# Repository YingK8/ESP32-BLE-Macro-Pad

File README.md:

# ESP32 BLE HID Macropad

A compact, programmable macropad with Bluetooth connectivity, featuring 6 mechanical keys and a rotary encoder for media control.

## Features

- 6-key mechanical switch matrix
- Rotary encoder for volume/scroll control
- Bluetooth HID (no drivers required)
- ST7789 240×280 screen driven by a desktop companion app over USB
- Productivity apps — pomodoro, class/assignment agenda, now playing, system stats —
  that live on the PC, so adding one needs no reflashing

## Hardware

| Component | Quantity |
|-----------|----------|
| ESP32-C3 Dev Board | 1 |
| Mechanical Keyswitches | 6 |
| Rotary Encoder | 1 |
| 1N4148 Diodes | 6 |
| ST7789 240×280 SPI display | 1 |

## Pinout

Authoritative source is [`macro-pad/include/Config.h`](macro-pad/include/Config.h).

| Function | ESP32 Pin |
|----------|-----------|
| Row 1 | GPIO 1 |
| Row 2 | GPIO 5 |
| Col 1 | GPIO 4 |
| Col 2 | GPIO 21 |
| Col 3 | GPIO 8 |
| Encoder A | GPIO 3 |
| Encoder B | GPIO 10 |
| TFT SCK / MOSI | GPIO 7 / 6 |
| TFT DC / CS / RST | GPIO 2 / 0 / 9 |
| TFT backlight | GPIO 20 |

> GPIO21 is UART0 TX on the ESP32-C3. The `ARDUINO_USB_CDC_ON_BOOT` build flag
> routes `Serial` to native USB to free it; if the two column-1 keys do not
> register, that pin is the reason.

## Installation

1. Wire components according to the pinout table.
2. Flash the firmware (PlatformIO pulls the libraries itself):
   ```bash
   cd macro-pad && pio run -t upload
   ```
3. Set up the desktop app:
   ```bash
   cd macro-pad/host && uv sync && uv run macropad run
   ```

## Usage

1. Power on the macropad and pair with "ESP32 MacroPad" via Bluetooth — this
   carries the keyboard macros.
2. Plug it in over USB — this carries the screen. The menubar icon shows the link
   state and lets you switch apps.
3. Default layout:

   | | Col 1 (GPIO4) | Col 2 (GPIO21) | Col 3 (GPIO8) |
   |---|---|---|---|
   | **Row 1** | previous app | ⌘⇧4 screenshot | next app |
   | **Row 2** | action A | ⌘Space Spotlight | action B |

   The encoder controls volume, unless the active app asks for it.

## Architecture

The pad is a dumb character-cell terminal: the PC renders each app to text lines
and pushes finished frames down the wire, and the pad reports key and encoder
events back. App logic, API tokens and text never touch the ESP32, which is what
keeps the firmware at ~48% of the C3's 1.25 MB app slot no matter how many apps
exist.

- [`macro-pad/PROTOCOL.md`](macro-pad/PROTOCOL.md) — wire format, key ids, grid maths
- [`macro-pad/host/README.md`](macro-pad/host/README.md) — desktop app, apps, writing your own

## Customization

Macro keys are the `Key::combo(...)` entries in
[`macro-pad/src/main.cpp`](macro-pad/src/main.cpp); `Key::app(...)` entries are
forwarded to the host instead of being typed. Everything else — what each screen
shows, what the action keys do — is Python in `macro-pad/host/`.

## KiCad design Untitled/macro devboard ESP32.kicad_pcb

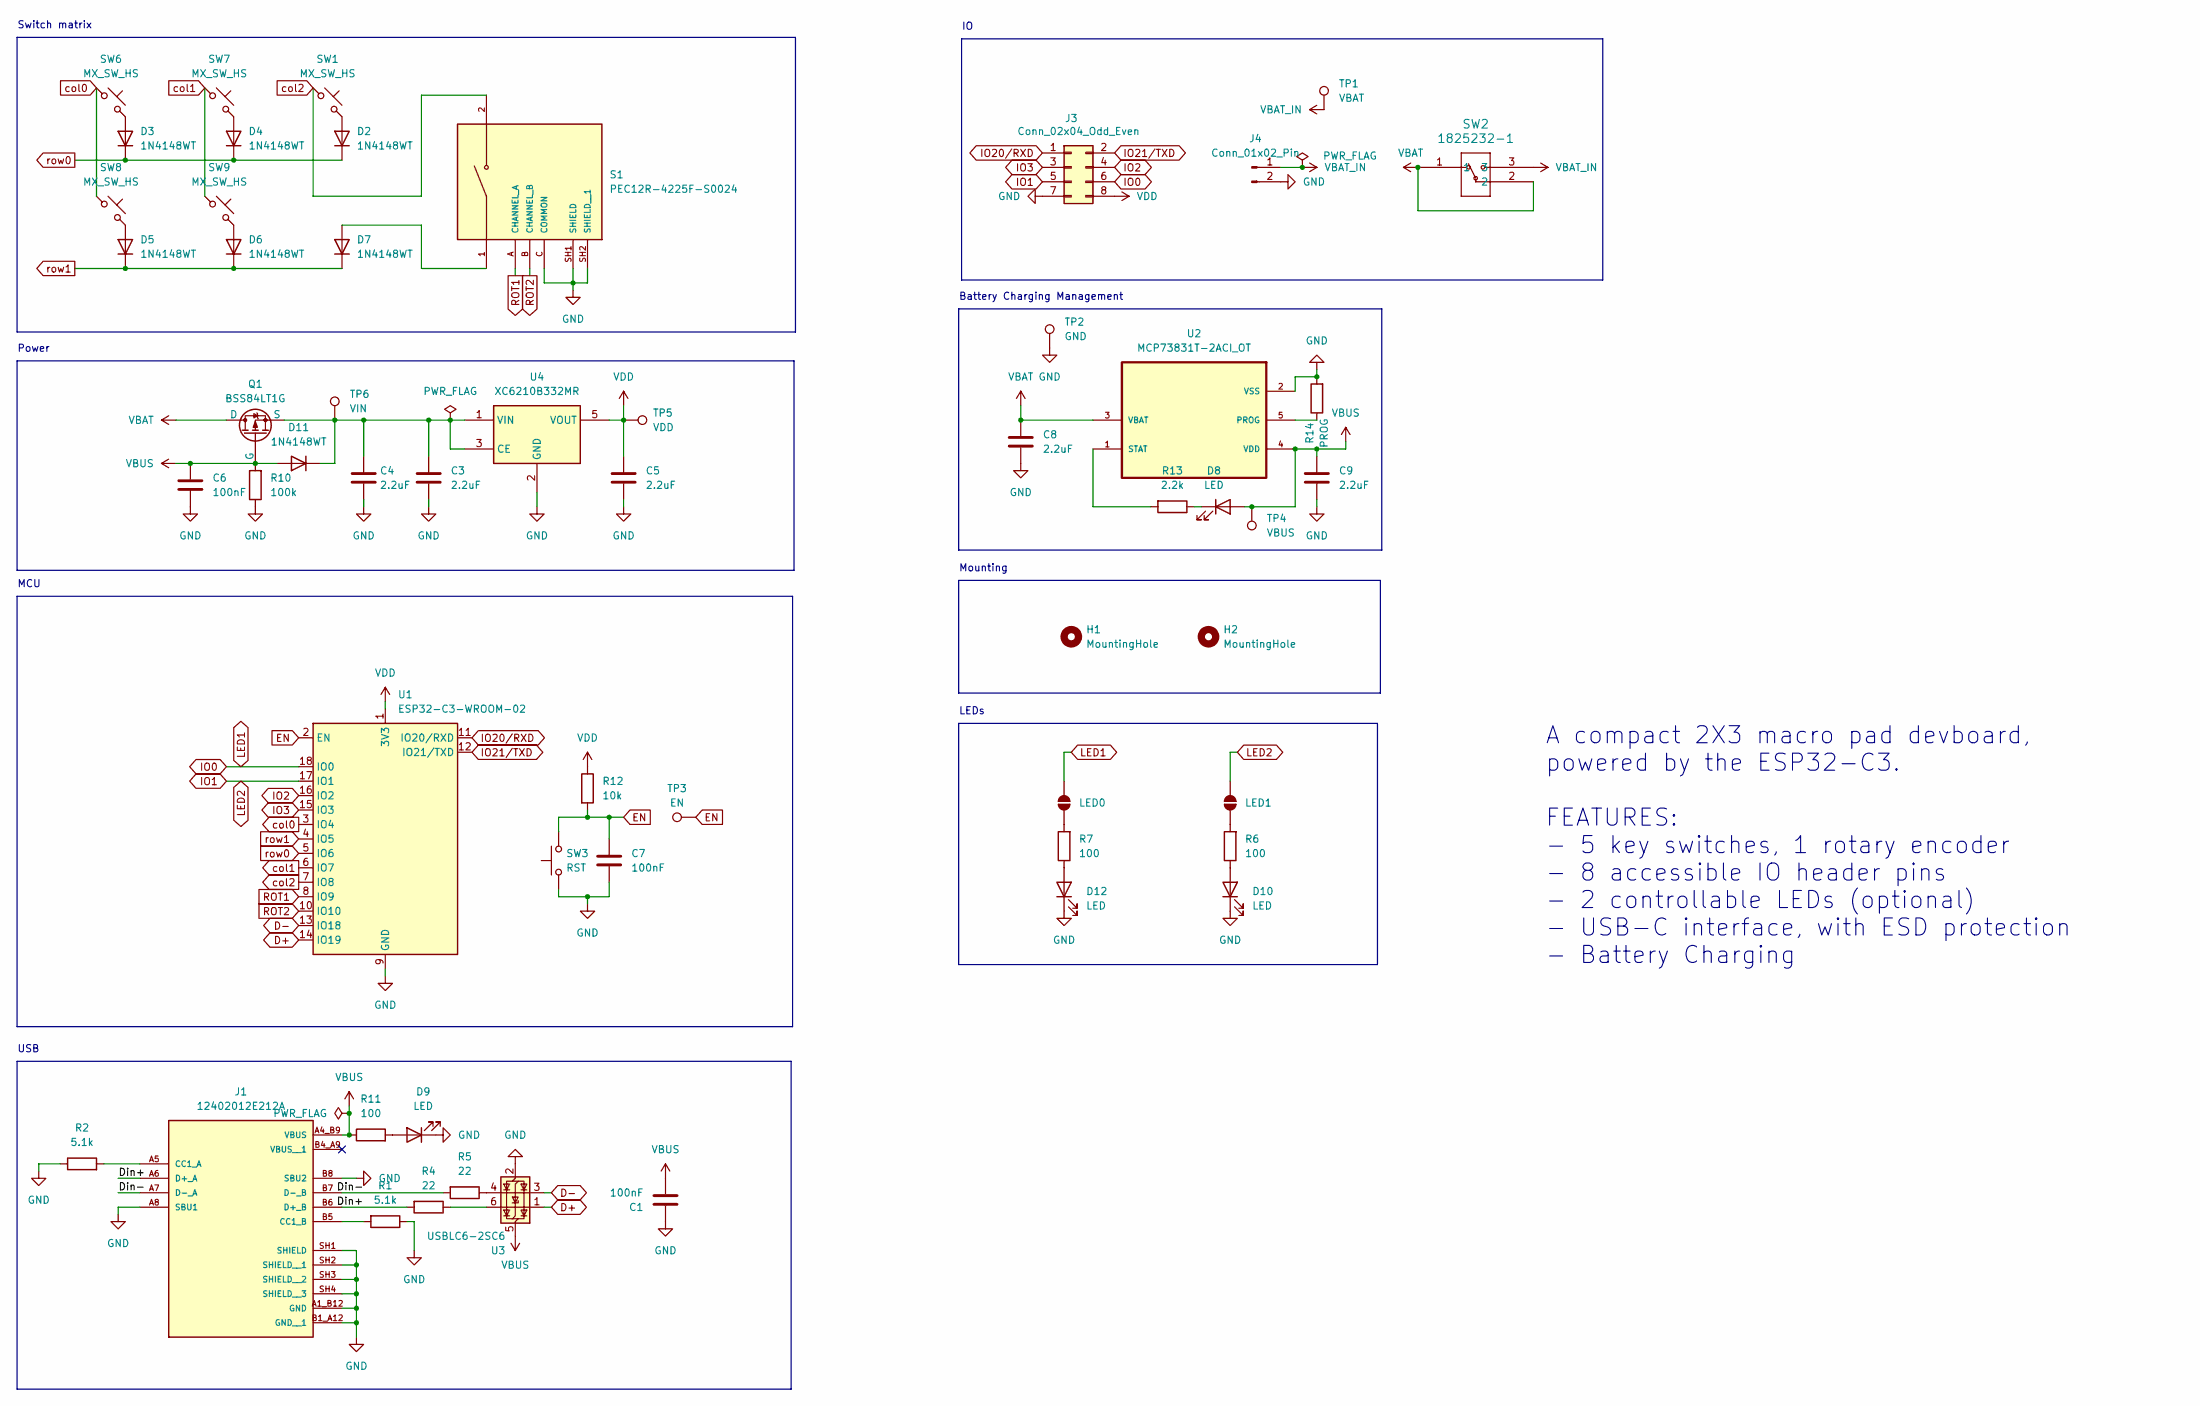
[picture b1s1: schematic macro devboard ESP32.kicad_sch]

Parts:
C1, C6, C7: 100nF; C_0603_1608Metric_Pad1.08x0.95mm_HandSolder
C3, C4, C5, C8, C9: 2.2uF; C_0603_1608Metric_Pad1.08x0.95mm_HandSolder
D2, D3, D4, D5, D6, D7, D11: 1N4148WT; D_SOD-323F
D8, D9, D10, D12: LED; LED_0805_2012Metric_Pad1.15x1.40mm_HandSolder
H1, H2: MountingHole; MountingHole_2.7mm_M2.5
J1: 12402012E212A; AMPHENOL_12402012E212A; PARTREV 4
J3: Conn_02x04_Odd_Even; PinSocket_2x04_P2.54mm_Vertical
J4: Conn_01x02_Pin; JST_PH_S2B-PH-K_1x02_P2.00mm_Horizontal
LED0, LED1: SolderJumper_2_Open; SolderJumper-2_P1.3mm_Open_RoundedPad1.0x1.5mm
Q1: BSS84LT1G; TSOT-23_HandSoldering
R1, R2: 5.1k; R_0603_1608Metric_Pad0.98x0.95mm_HandSolder
R4, R5: 22; R_0603_1608Metric_Pad0.98x0.95mm_HandSolder
R6, R7, R11: 100; R_0603_1608Metric_Pad0.98x0.95mm_HandSolder
R10: 100k; R_0603_1608Metric_Pad0.98x0.95mm_HandSolder
R12: 10k; R_0603_1608Metric_Pad0.98x0.95mm_HandSolder
R13: 2.2k; R_0603_1608Metric_Pad0.98x0.95mm_HandSolder
R14: PROG; R_0603_1608Metric_Pad0.98x0.95mm_HandSolder
S1: PEC12R-4225F-S0024; XDCR_PEC12R-4225F-S0024; PARTREV 07/21
SW1, SW6, SW7, SW8, SW9: MX_SW_HS; Kailh_socket_MX_optional
SW2: 1825232-1; 1825232-1_TEC
SW3: RST; SW_Tactile_SPST_NO_Straight_CK_PTS636Sx25SMTRLFS
TP1: VBAT; TestPoint_Pad_D2.0mm
TP2: GND; TestPoint_Pad_D2.0mm
TP3: EN; TestPoint_Pad_D2.0mm
TP4: VBUS; TestPoint_Pad_D2.0mm
TP5: VDD; TestPoint_Pad_D2.0mm
TP6: VIN; TestPoint_Pad_D2.0mm
U1: ESP32-C3-WROOM-02
U2: MCP73831T-2ACI_OT; SOT95P280X145-5N; MPN MCP73831T-2ACI/OT
U3: USBLC6-2SC6; SOT-23-6_Handsoldering
U4: XC6210B332MR; SC-74A-5_1.55x2.9mm_P0.95mm

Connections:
/Din+: J1.A6 (D+_A), J1.B6 (D+_B), R4.2
/Din-: J1.A7 (D-_A), J1.B7 (D-_B), R5.2
D+: U1.14 (IO19), U3.1 (I/O1)
D-: U1.13 (IO18), U3.3 (I/O2)
EN: C7.2, R12.2, SW3.2, TP3.1, U1.2 (EN)
GND: C1.2, C3.1, C4.1, C5.1, C6.1, C7.1, C8.1, C9.2, D9.1 (K), D10.1 (K), D12.1 (K), J1.A1_B12 (GND), J1.A8 (SBU1), J1.B1_A12 (GND__1), J1.B8 (SBU2), J1.SH1 (SHIELD), J1.SH2 (SHIELD__1), J1.SH3 (SHIELD__2), J1.SH4 (SHIELD__3), J3.7, J4.2, R1.1, R2.1, R10.1, R14.2, S1.C (COMMON), S1.SH1 (SHIELD), S1.SH2 (SHIELD__1), SW3.1, TP2.1, U1.9 (GND), U1.19 (GND), U2.2 (VSS), U3.2 (GND), U4.2 (GND)
IO0: J3.6, LED0.2 (B), U1.18 (IO0)
IO1: J3.5, LED1.2 (B), U1.17 (IO1)
IO2: J3.4, U1.16 (IO2)
IO3: J3.3, U1.15 (IO3)
IO20/RXD: J3.1, U1.11 (IO20/RXD)
IO21/TXD: J3.2, U1.12 (IO21/TXD)
unnamed: D2.2 (A), SW1.2
unnamed: D3.2 (A), SW6.2
unnamed: D4.2 (A), SW7.2
unnamed: D5.2 (A), SW8.2
unnamed: D6.2 (A), SW9.2
unnamed: D7.2 (A), S1.1
unnamed: D8.1 (K), R13.1
unnamed: D9.2 (A), R11.2
unnamed: D10.2 (A), R6.1
unnamed: C3.2, C4.2, D11.1 (K), Q1.2 (S), TP6.1, U4.1 (VIN), U4.3 (CE)
unnamed: D12.2 (A), R7.1
unnamed: J1.A5 (CC1_A), R2.2
unnamed: J1.B5 (CC1_B), R1.2
unnamed: LED0.1 (A), R7.2
unnamed: LED1.1 (A), R6.2
unnamed: R4.1, U3.6 (I/O1)
unnamed: R5.1, U3.4 (I/O2)
unnamed: R14.1, U2.5 (PROG)
unnamed: R13.2, U2.1 (STAT)
ROT1: S1.A (CHANNEL_A), U1.8 (IO9)
ROT2: S1.B (CHANNEL_B), U1.10 (IO10)
VBAT: C8.2, Q1.3 (D), SW2.1, SW2.2, U2.3 (VBAT)
VBAT_IN: J4.1, SW2.3, TP1.1
VBUS: C1.1, C6.2, C9.1, D8.2 (A), D11.2 (A), J1.A4_B9 (VBUS), Q1.1 (G), R10.2, R11.1, TP4.1, U2.4 (VDD), U3.5 (VBUS)
VDD: C5.2, J3.8, R12.1, TP5.1, U1.1 (3V3), U4.5 (VOUT)
col0: SW6.1, SW8.1, U1.3 (IO4)
col1: SW7.1, SW9.1, U1.6 (IO7)
col2: S1.2, SW1.1, U1.7 (IO8)
row0: D2.1 (K), D3.1 (K), D4.1 (K), U1.5 (IO6)
row1: D5.1 (K), D6.1 (K), D7.1 (K), U1.4 (IO5)

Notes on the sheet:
LEDs
Mounting
A compact 2X3 macro pad devboard, powered by the ESP32-C3. FEATURES: - 5 key switches, 1 rotary encoder - 8 accessible IO header pins - 2 controllable LEDs (optional) - USB-C interface, with ESD protection - Battery Charging
USB
Power
Switch matrix
MCU
Battery Charging Management

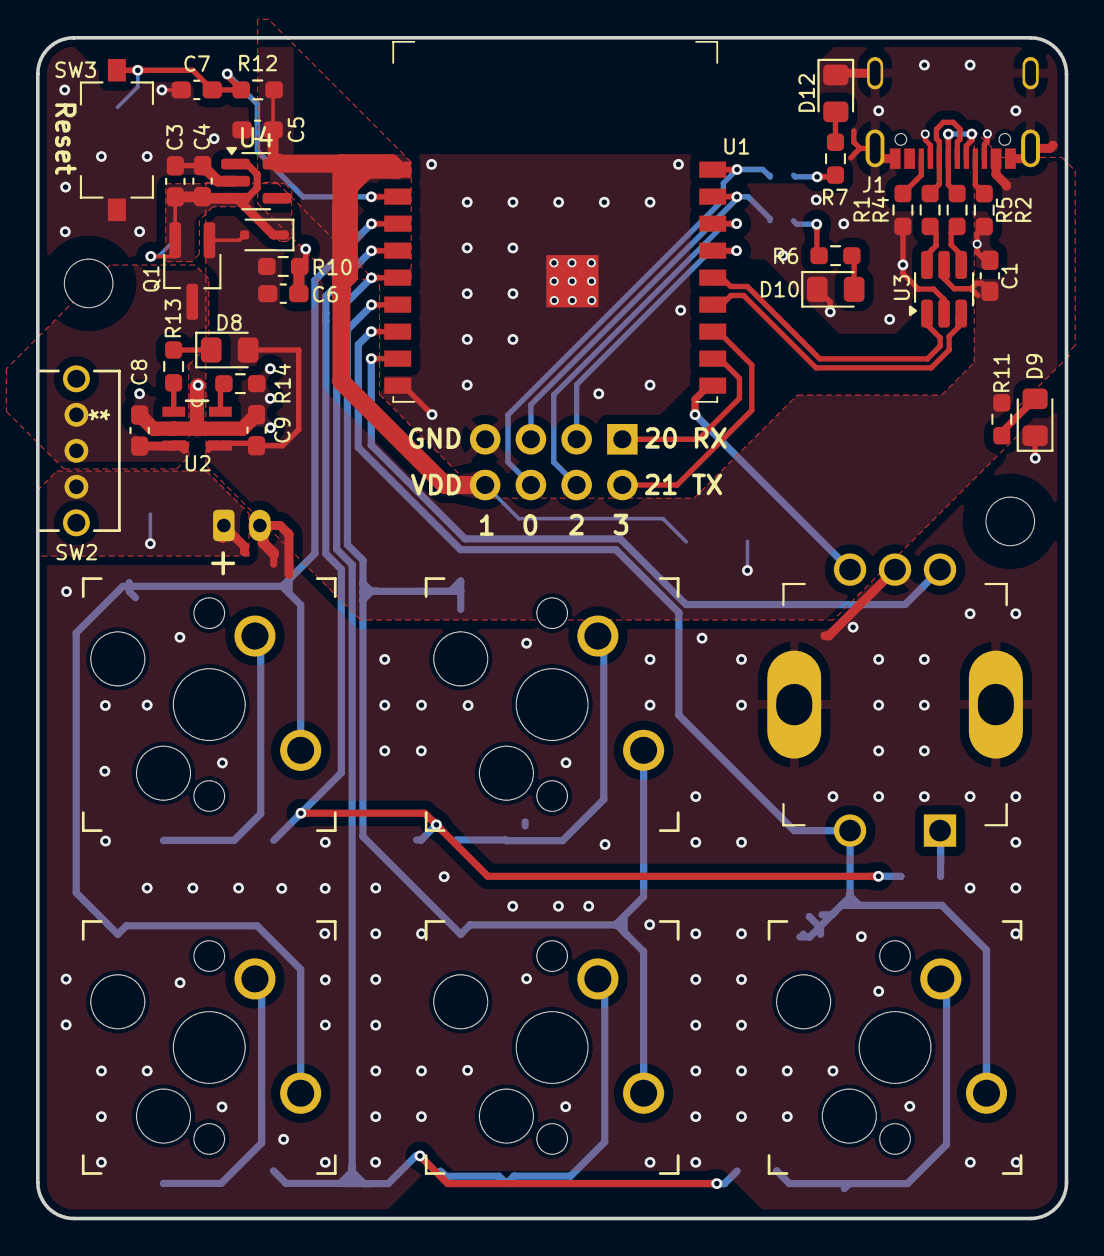
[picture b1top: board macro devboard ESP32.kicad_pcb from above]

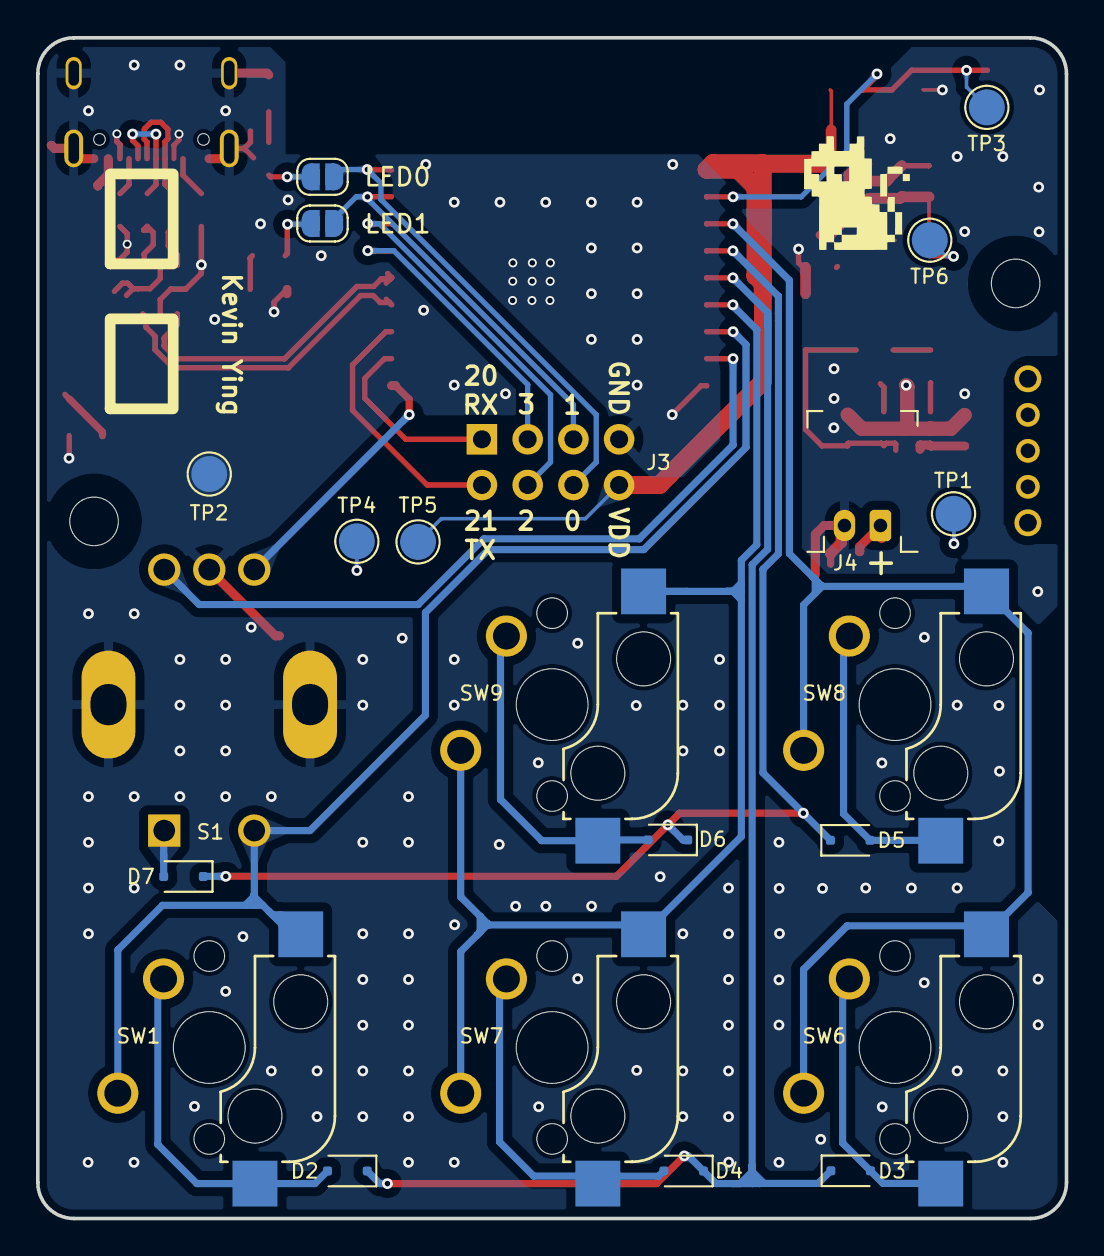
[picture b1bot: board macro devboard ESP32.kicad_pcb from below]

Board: 4 copper layers, 57.1 x 65.6 mm, 56 parts (16 on the bottom side), 42 nets.

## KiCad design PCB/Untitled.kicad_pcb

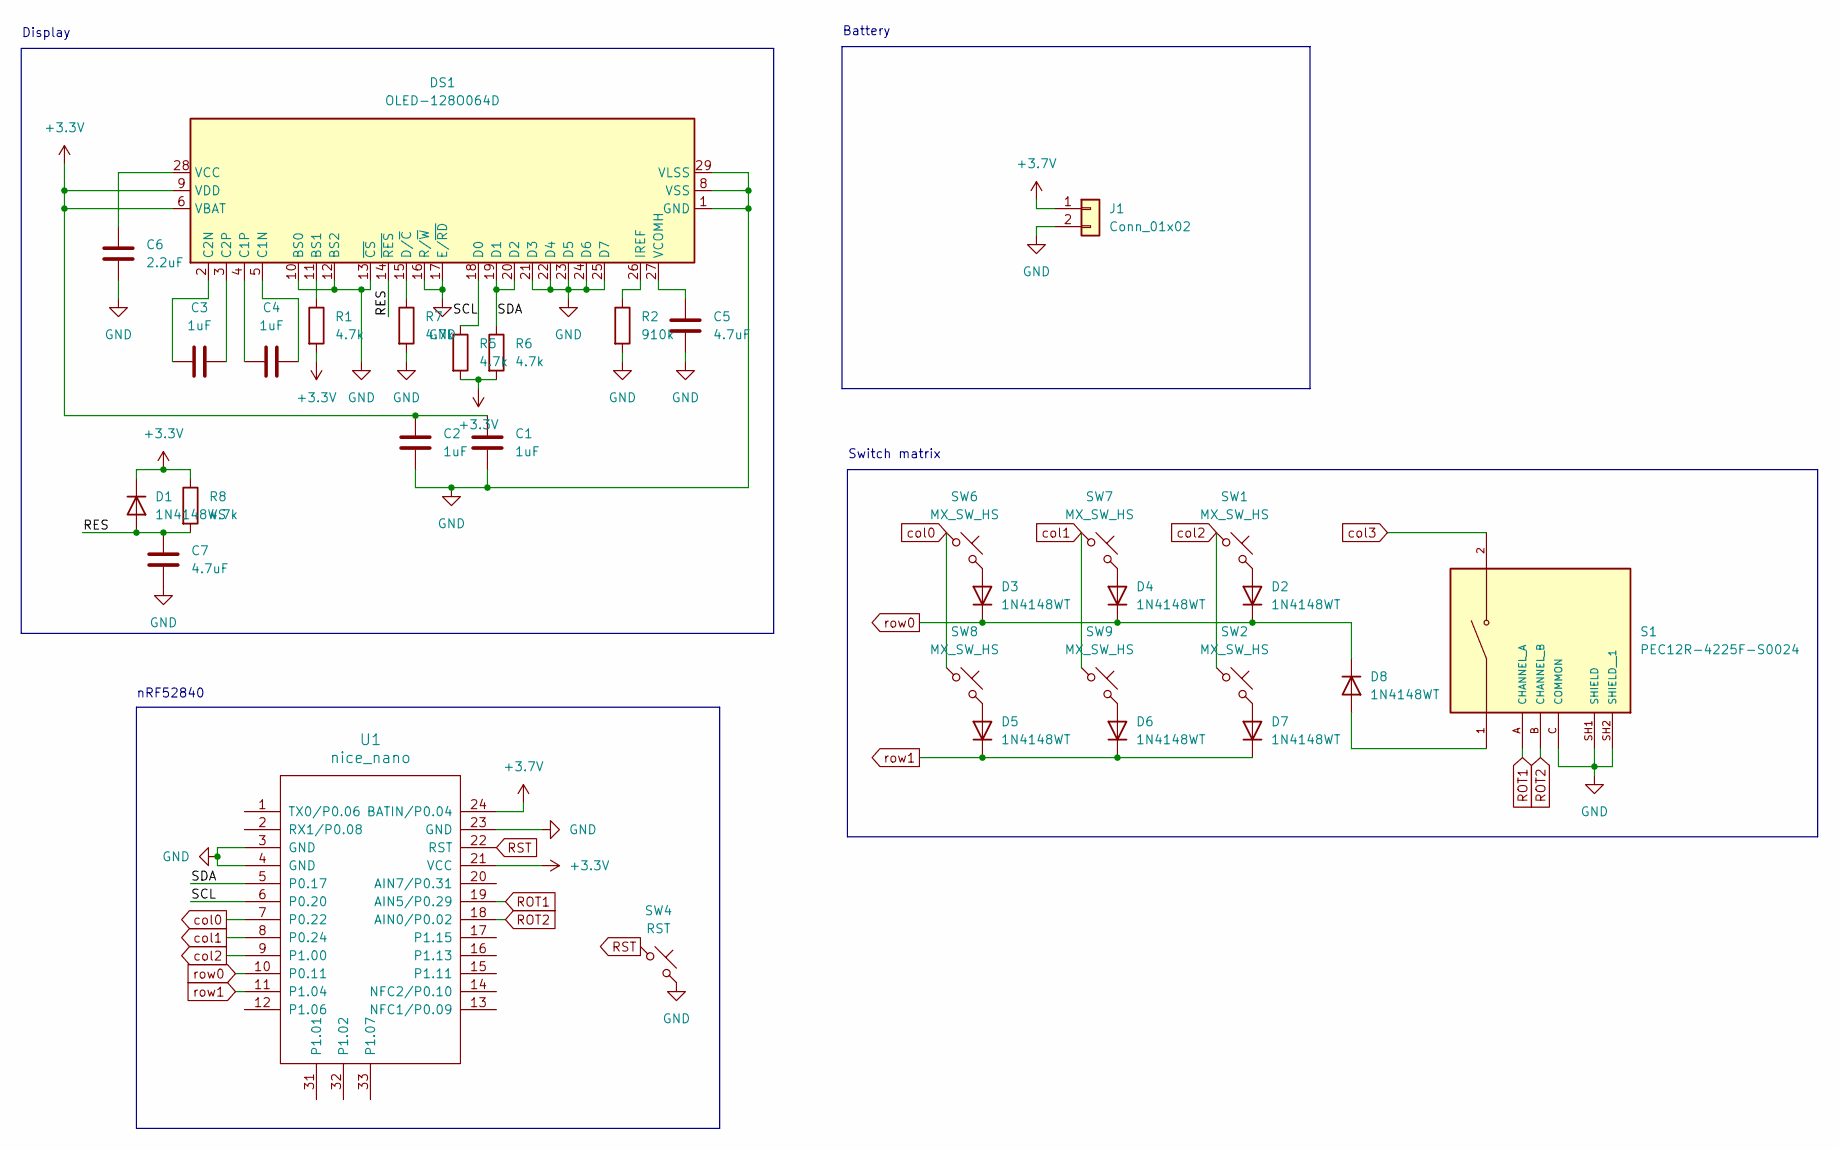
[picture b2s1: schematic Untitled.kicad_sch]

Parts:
C1, C2, C3, C4: 1uF; C_0805_2012Metric_Pad1.18x1.45mm_HandSolder
C5, C7: 4.7uF; C_0805_2012Metric_Pad1.18x1.45mm_HandSolder
C6: 2.2uF; C_0805_2012Metric_Pad1.18x1.45mm_HandSolder
D1: 1N4148WS; D_SOD-323F
D2, D3, D4, D5, D6, D7, D8: 1N4148WT; D_SOD-323F
DS1: OLED-128O064D
J1: Conn_01x02; JST_PH_S2B-PH-K_1x02_P2.00mm_Horizontal
R1, R5, R6, R7, R8: 4.7k; R_0805_2012Metric_Pad1.20x1.40mm_HandSolder
R2: 910k; R_0805_2012Metric_Pad1.20x1.40mm_HandSolder
S1: PEC12R-4225F-S0024; XDCR_PEC12R-4225F-S0024; PARTREV 07/21
SW1, SW2, SW6, SW7, SW8, SW9: MX_SW_HS; Kailh_socket_MX
SW4: RST; SW_Tactile_SPST_NO_Straight_CK_PTS636Sx25SMTRLFS
U1: nice_nano

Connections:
+3.3V: C1.2, C2.2, D1.1 (K), DS1.6 (VBAT), DS1.9 (VDD), R1.2, R5.2, R6.2, R8.1, U1.21 (VCC)
+3.7V: J1.1, U1.24 (BATIN/P0.04)
/RES: C7.2, D1.2 (A), DS1.14 (~RES), R8.2
/SCL: DS1.18 (D0), R5.1, U1.6 (P0.20)
/SDA: DS1.19 (D1), DS1.20 (D2), R6.1, U1.5 (P0.17)
GND: C1.1, C2.1, C5.1, C6.1, C7.1, DS1.1 (GND), DS1.8 (VSS), DS1.10 (BS0), DS1.12 (BS2), DS1.13 (~CS), DS1.16 (R/~W), DS1.17 (E/~RD), DS1.21 (D3), DS1.22 (D4), DS1.23 (D5), DS1.24 (D6), DS1.25 (D7), DS1.29 (VLSS), DS1.30 (GND), J1.2, R2.2, R7.2, S1.C (COMMON), S1.SH1 (SHIELD), S1.SH2 (SHIELD__1), SW4.2, U1.3 (GND), U1.4 (GND), U1.23 (GND)
unnamed: D2.2 (A), SW1.2
unnamed: D3.2 (A), SW6.2
unnamed: D4.2 (A), SW7.2
unnamed: D5.2 (A), SW8.2
unnamed: D6.2 (A), SW9.2
unnamed: D7.2 (A), SW2.2
unnamed: D8.2 (A), S1.1
unnamed: DS1.11 (BS1), R1.1
unnamed: C4.2, DS1.5 (C1N)
unnamed: C4.1, DS1.4 (C1P)
unnamed: C3.1, DS1.2 (C2N)
unnamed: C3.2, DS1.3 (C2P)
unnamed: DS1.15 (D/~C), R7.1
unnamed: DS1.26 (IREF), R2.1
unnamed: C6.2, DS1.28 (VCC)
unnamed: C5.2, DS1.27 (VCOMH)
ROT1: S1.A (CHANNEL_A), U1.19 (AIN5/P0.29)
ROT2: S1.B (CHANNEL_B), U1.18 (AIN0/P0.02)
RST: SW4.1, U1.22 (RST)
col0: SW6.1, SW8.1, U1.7 (P0.22)
col1: SW7.1, SW9.1, U1.8 (P0.24)
col2: SW1.1, SW2.1, U1.9 (P1.00)
col3: S1.2
row0: D2.1 (K), D3.1 (K), D4.1 (K), D8.1 (K), U1.10 (P0.11)
row1: D5.1 (K), D6.1 (K), D7.1 (K), U1.11 (P1.04)

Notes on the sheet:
Battery
Display
Switch matrix
nRF52840

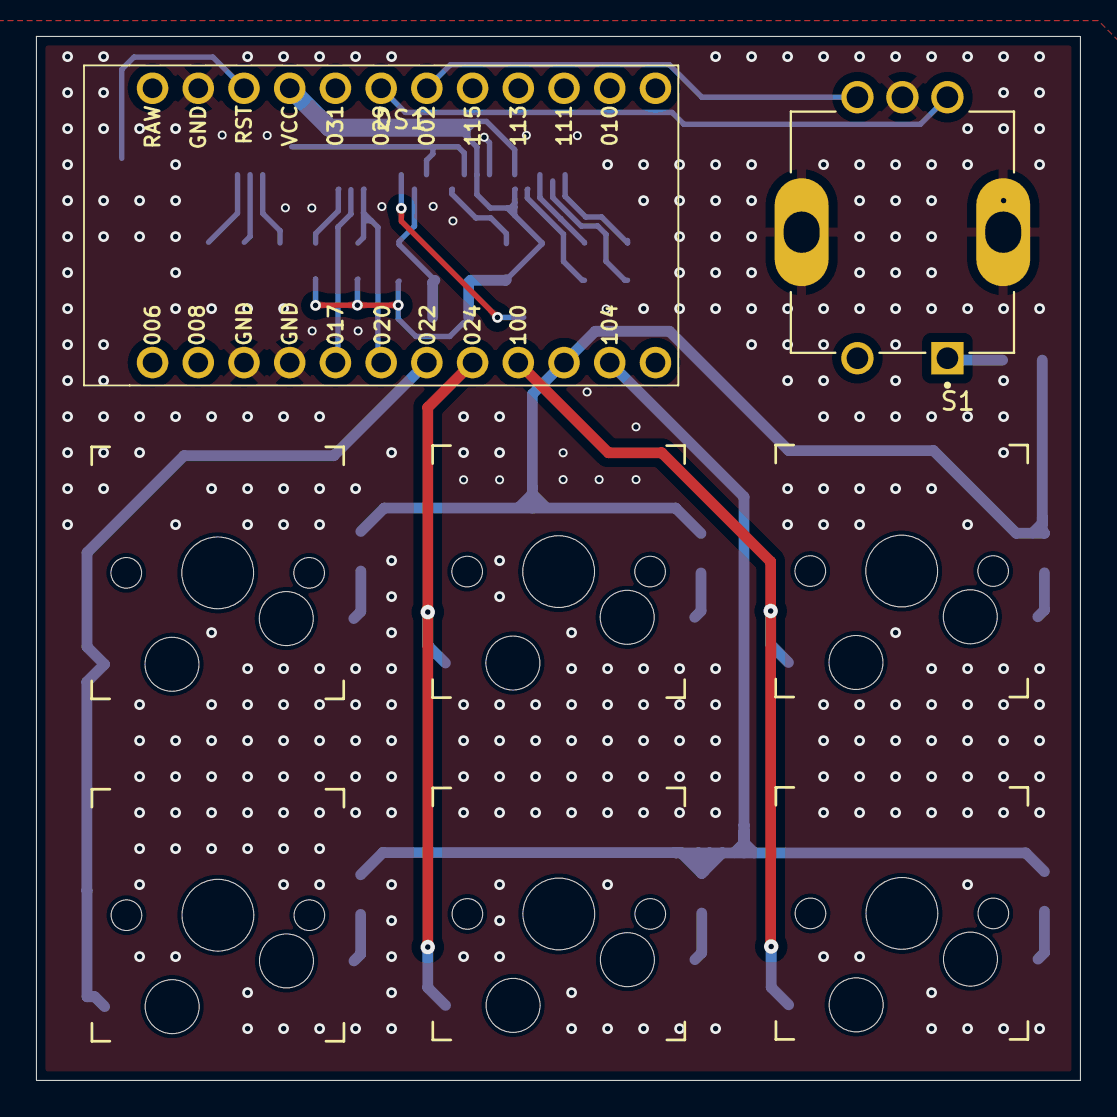
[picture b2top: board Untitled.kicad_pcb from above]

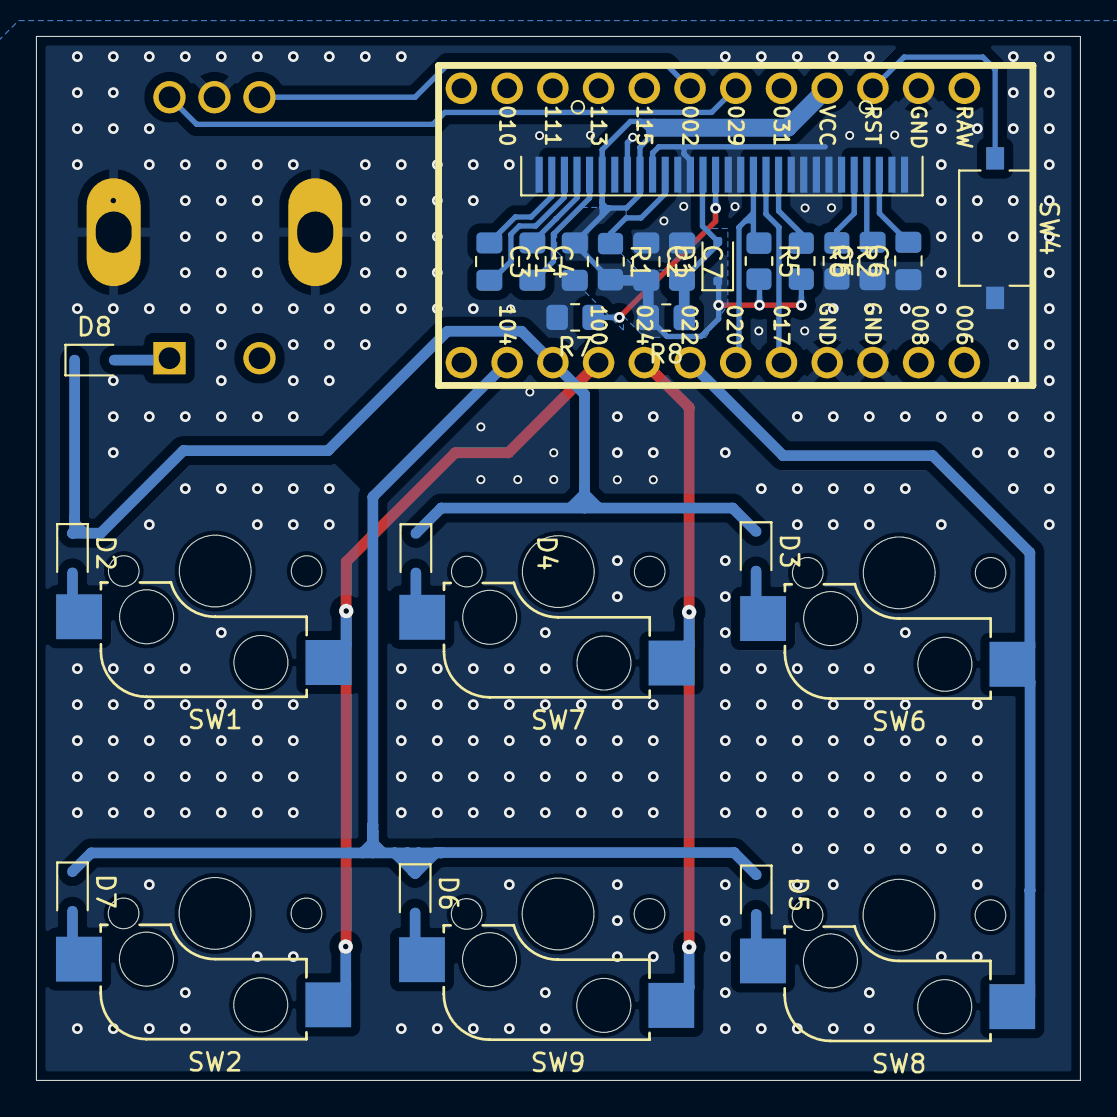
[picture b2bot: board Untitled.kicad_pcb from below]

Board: 2 copper layers, 58.0 x 58.0 mm, 31 parts (23 on the bottom side), 29 nets.

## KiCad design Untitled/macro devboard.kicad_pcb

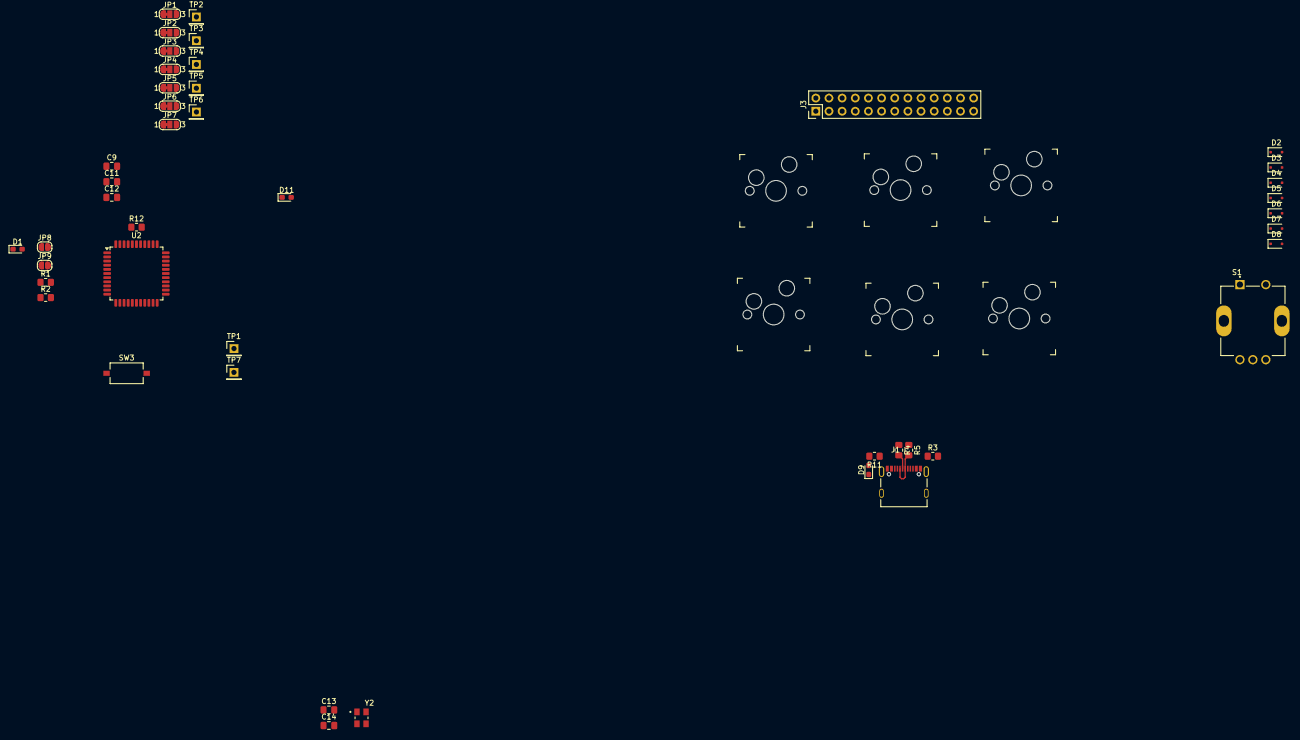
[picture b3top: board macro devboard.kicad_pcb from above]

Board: 2 copper layers, 50 parts (0 on the bottom side), 58 nets.

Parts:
C9, C11, C12: 1uF; C_0805_2012Metric_Pad1.18x1.45mm_HandSolder
C13, C14: 18pF; C_0805_2012Metric_Pad1.18x1.45mm_HandSolder
D1, D9, D11: LED; LED_0603_1608Metric_Pad1.05x0.95mm_HandSolder
D2, D3, D4, D5, D6, D7, D8: 1N4148WT; D_SOD-323F
J1: 12402012E212A; AMPHENOL_12402012E212A
J3: Conn_02x13_Counter_Clockwise; PinHeader_2x13_P2.54mm_Vertical
JP1, JP2, JP3, JP4, JP5, JP6, JP7: SolderJumper_3_Bridged12; SolderJumper-3_P1.3mm_Bridged12_RoundedPad1.0x1.5mm_NumberL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
JP8, JP9: SolderJumper_2_Open; SolderJumper-2_P1.3mm_Open_RoundedPad1.0x1.5mm
R1, R2, R11: 100; R_0805_2012Metric_Pad1.20x1.40mm_HandSolder
R3: 4.7k; R_0805_2012Metric_Pad1.20x1.40mm_HandSolder
R4, R5: 22; R_0805_2012Metric_Pad1.20x1.40mm_HandSolder
R12: 10k; R_0805_2012Metric_Pad1.20x1.40mm_HandSolder
S1: PEC12R-4225F-S0024; XDCR_PEC12R-4225F-S0024
SW1, SW2, SW6, SW7, SW8, SW9: MX_SW_HS; Kailh_socket_MX
SW3: RST; SW_Tactile_SPST_NO_Straight_CK_PTS636Sx25SMTRLFS
TP1, TP2, TP3, TP4, TP5, TP6, TP7: TestPoint; PinHeader_1x01_P2.54mm_Vertical
U2: ATmega32U4-A; TQFP-44_10x10mm_P0.8mm
Y2: ABM8-16.000MHz-D1X-T; XTAL_ABM8-16.000MHz-D1X-T

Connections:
+5V: J1.A4_B9 (VBUS), J3.1, J3.25, J3.26, R11.1, R12.2, U2.14 (VCC), U2.24 (AVCC), U2.34 (VCC), U2.44 (AVCC)
/CC1: J1.A5 (CC1_A), J1.B5 (CC1_B), R3.1
/Din+: J1.A6 (D+_A), J1.B6 (D+_B), R4.2
/Din-: J1.A7 (D-_A), J1.B7 (D-_B), R5.2
/RESET: R12.1, SW3.1, U2.13 (~RESET)
/UVCC: C11.1, U2.2 (UVCC), U2.7 (VBUS)
/XTAL1: C13.1, U2.17 (XTAL1), Y2.1
/XTAL2: C14.1, U2.16 (XTAL2), Y2.3
D+: R4.1, U2.4 (D+)
D-: R5.1, U2.3 (D-)
GND: C9.1, C11.2, C12.2, C13.2, C14.2, D1.1 (K), D9.1 (K), D11.1 (K), J1.A1_B12 (GND), J1.A8 (SBU1), J1.B1_A12 (GND__1), J1.B8 (SBU2), J1.SH1 (SHIELD), J1.SH2 (SHIELD__1), J1.SH3 (SHIELD__2), J1.SH4 (SHIELD__3), J3.7, J3.13, J3.16, J3.19, R3.2, S1.C (COMMON), S1.SH1 (SHIELD), S1.SH2 (SHIELD__1), SW3.2, U2.5 (UGND), U2.15 (GND), U2.23 (GND), U2.33 (~HWB/PE2), U2.35 (GND), U2.43 (GND), Y2.2 (GND), Y2.4 (GND__1)
unnamed: D1.2 (A), R1.1
unnamed: D2.2 (A), SW1.2
unnamed: D3.2 (A), SW6.2
unnamed: D4.2 (A), SW7.2
unnamed: D5.2 (A), SW8.2
unnamed: D6.2 (A), SW9.2
unnamed: D7.2 (A), SW2.2
unnamed: D8.2 (A), S1.1
unnamed: D9.2 (A), R11.2
unnamed: D11.2 (A), R2.1
unnamed: JP1.1 (A), TP5.1, U2.29 (PB5)
unnamed: JP2.1 (A), TP6.1, U2.30 (PB6)
unnamed: JP3.1 (A), TP4.1, U2.28 (PB4)
unnamed: JP4.1 (A), TP2.1, U2.31 (PC6)
unnamed: JP5.1 (A), TP3.1, U2.32 (PC7)
unnamed: JP6.1 (A), TP1.1, U2.26 (PD6)
unnamed: JP7.1 (A), TP7.1, U2.27 (PD7)
unnamed: JP8.1 (A), R1.2
unnamed: JP9.1 (A), R2.2
unnamed: JP9.2 (B), U2.25 (PD4)
unnamed: C12.1, U2.42 (AREF)
unnamed: C9.2, U2.6 (UCAP)
PB0/SS: J3.24, U2.8 (PB0)
PB1/SCK: J3.23, U2.9 (PB1)
PB2/MOSI: J3.22, U2.10 (PB2)
PB3/MISO: J3.21, U2.11 (PB3)
PB7/RTS: J3.20, U2.12 (PB7)
PC6: J3.15, JP4.3 (B)
PC7: J3.14, JP5.3 (B)
PD0/SCL: J3.12, U2.18 (PD0)
PD1/SDA: J3.11, U2.19 (PD1)
PD2/RXD1: J3.10, U2.20 (PD2)
PD3/TXD1: J3.9, U2.21 (PD3)
PD5/CTS: J3.8, U2.22 (PD5)
PF0: J3.6, U2.41 (PF0)
PF1: J3.5, U2.40 (PF1)
PF4: J3.4, U2.39 (PF4)
PF5: J3.3, U2.38 (PF5)
PF6: J3.2, U2.37 (PF6)
PF7/LED1: J3.17, JP8.2 (B), U2.36 (PF7)
ROT1: JP6.2 (C), S1.A (CHANNEL_A)
ROT2: JP7.2 (C), S1.B (CHANNEL_B)
col0: JP3.2 (C), SW6.1, SW8.1
col1: JP1.2 (C), SW7.1, SW9.1
col2: JP2.2 (C), SW1.1, SW2.1
row0: D2.1 (K), D3.1 (K), D4.1 (K), D8.1 (K), JP4.2 (C)
row1: D5.1 (K), D6.1 (K), D7.1 (K), JP5.2 (C)

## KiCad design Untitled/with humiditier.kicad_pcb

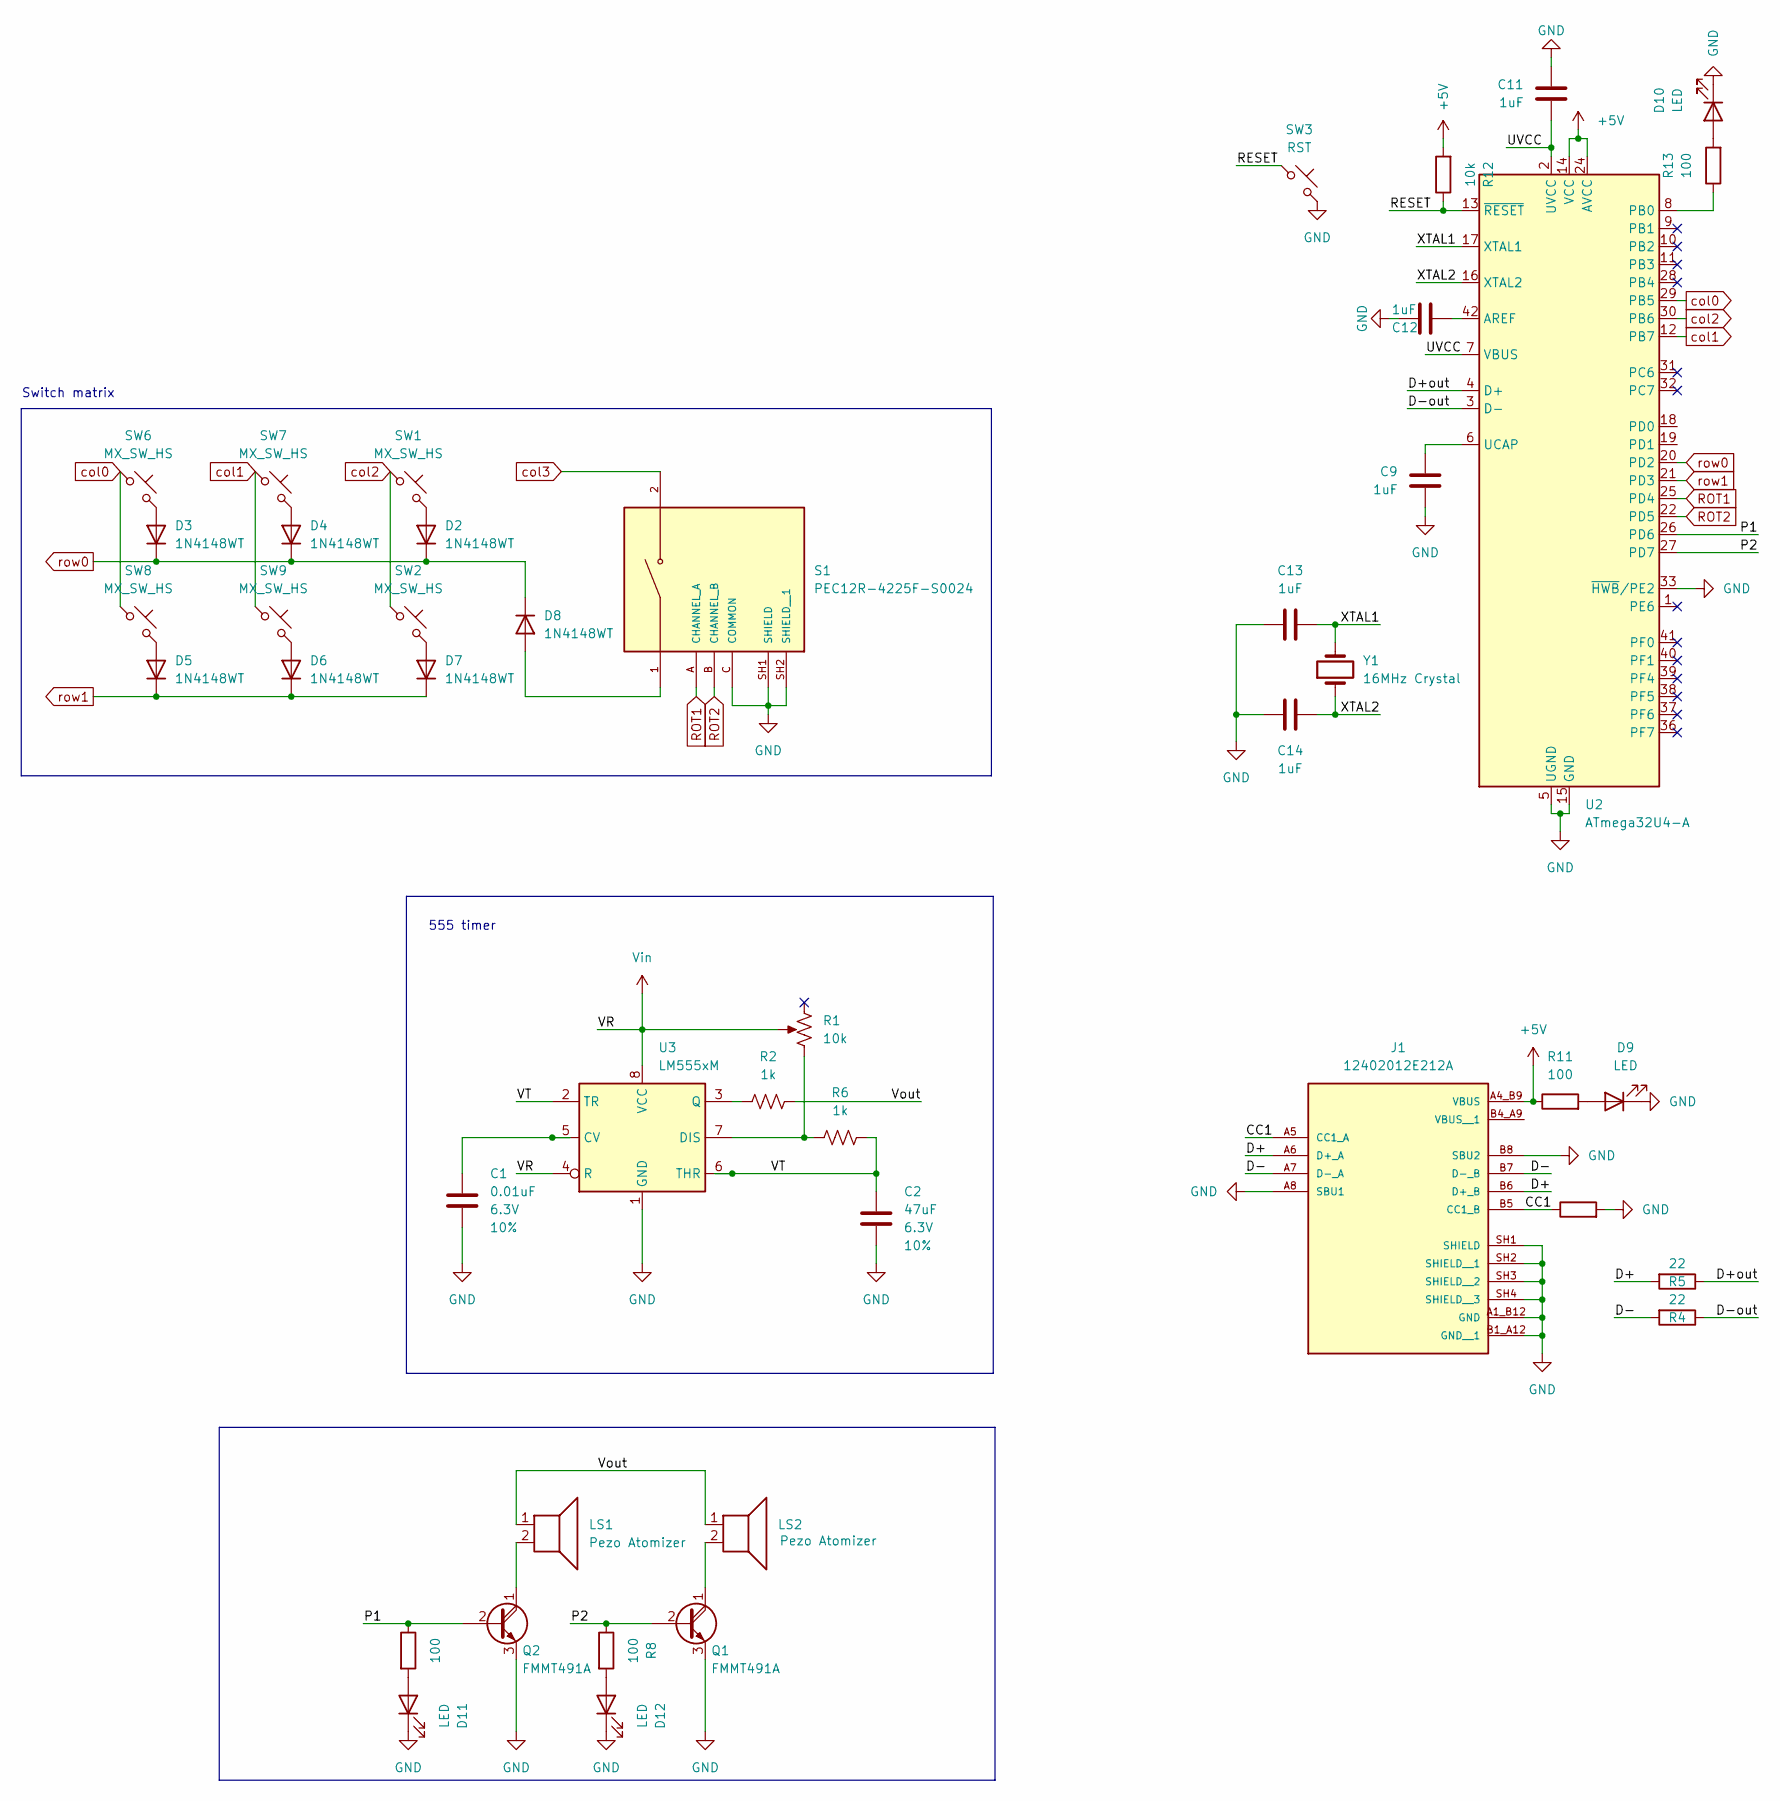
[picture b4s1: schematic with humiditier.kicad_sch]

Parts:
C1: 0.01uF; C_0805_2012Metric_Pad1.18x1.45mm_HandSolder; Voltage 6.3V; Tolerance 10%
C2: 47uF; C_0805_2012Metric_Pad1.18x1.45mm_HandSolder; Voltage 6.3V; Tolerance 10%
C9, C11, C12, C13, C14: 1uF; C_0805_2012Metric_Pad1.18x1.45mm_HandSolder
D2, D3, D4, D5, D6, D7, D8: 1N4148WT; D_SOD-323F
D9, D10, D11, D12: LED; LED_0603_1608Metric_Pad1.05x0.95mm_HandSolder
J1: 12402012E212A; AMPHENOL_12402012E212A; PARTREV 4
LS1, LS2: Pezo Atomizer; PinHeader_1x02_P2.54mm_Vertical
Q1, Q2: FMMT491A; TO-92_Inline
R1: 10k; TRIM_PV37W103C01B00; Mfg Part# 22AR10K
R2, R6: 1k; C_0805_2012Metric_Pad1.18x1.45mm_HandSolder
R3: 4.7k; R_0805_2012Metric_Pad1.20x1.40mm_HandSolder
R4, R5: 22; R_0805_2012Metric_Pad1.20x1.40mm_HandSolder
R7, R8, R11, R13: 100; R_0805_2012Metric_Pad1.20x1.40mm_HandSolder
R12: 10k; R_0805_2012Metric_Pad1.20x1.40mm_HandSolder
S1: PEC12R-4225F-S0024; XDCR_PEC12R-4225F-S0024; PARTREV 07/21
SW1, SW2, SW6, SW7, SW8, SW9: MX_SW_HS; Kailh_socket_MX
SW3: RST; SW_Tactile_SPST_NO_Straight_CK_PTS636Sx25SMTRLFS
U2: ATmega32U4-A; TQFP-44_10x10mm_P0.8mm
U3: LM555xM; SOIC-8_3.9x4.9mm_P1.27mm
Y1: 16MHz Crystal

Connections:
+5V: J1.A4_B9 (VBUS), R11.1, R12.2, U2.14 (VCC), U2.24 (AVCC), U2.34 (VCC), U2.44 (AVCC)
/CC1: J1.A5 (CC1_A), J1.B5 (CC1_B), R3.1
/D+: J1.A6 (D+_A), J1.B6 (D+_B), R5.2
/D+out: R5.1, U2.4 (D+)
/D-: J1.A7 (D-_A), J1.B7 (D-_B), R4.2
/D-out: R4.1, U2.3 (D-)
/P1: Q2.2 (B), R7.1, U2.26 (PD6)
/P2: Q1.2 (B), R8.1, U2.27 (PD7)
/RESET: R12.1, SW3.1, U2.13 (~RESET)
/UVCC: C11.1, U2.2 (UVCC), U2.7 (VBUS)
/VT: C2.1, R6.2, U3.2 (TR), U3.6 (THR)
/Vout: LS1.1, LS2.1, R2.2
/XTAL1: C13.1, U2.17 (XTAL1), Y1.2
/XTAL2: C14.1, U2.16 (XTAL2), Y1.1
GND: C1.2, C2.2, C9.1, C11.2, C12.2, C13.2, C14.2, D9.1 (K), D10.1 (K), D11.1 (K), D12.1 (K), J1.A1_B12 (GND), J1.A8 (SBU1), J1.B1_A12 (GND__1), J1.B8 (SBU2), J1.SH1 (SHIELD), J1.SH2 (SHIELD__1), J1.SH3 (SHIELD__2), J1.SH4 (SHIELD__3), Q1.3 (E), Q2.3 (E), R3.2, S1.C (COMMON), S1.SH1 (SHIELD), S1.SH2 (SHIELD__1), SW3.2, U2.5 (UGND), U2.15 (GND), U2.23 (GND), U2.33 (~HWB/PE2), U2.35 (GND), U2.43 (GND), U3.1 (GND)
unnamed: D2.2 (A), SW1.2
unnamed: D3.2 (A), SW6.2
unnamed: D4.2 (A), SW7.2
unnamed: D5.2 (A), SW8.2
unnamed: D6.2 (A), SW9.2
unnamed: D7.2 (A), SW2.2
unnamed: D8.2 (A), S1.1
unnamed: D9.2 (A), R11.2
unnamed: D10.2 (A), R13.2
unnamed: D11.2 (A), R7.2
unnamed: D12.2 (A), R8.2
unnamed: LS2.2, Q1.1 (C)
unnamed: LS1.2, Q2.1 (C)
unnamed: C12.1, U2.42 (AREF)
unnamed: R13.1, U2.8 (PB0)
unnamed: C9.2, U2.6 (UCAP)
unnamed: C1.1, U3.5 (CV)
unnamed: R1.1, R6.1, U3.7 (DIS)
unnamed: R2.1, U3.3 (Q)
ROT1: S1.A (CHANNEL_A), U2.25 (PD4)
ROT2: S1.B (CHANNEL_B), U2.22 (PD5)
Vin: R1.2, U3.4 (R), U3.8 (VCC)
col0: SW6.1, SW8.1, U2.29 (PB5)
col1: SW7.1, SW9.1, U2.12 (PB7)
col2: SW1.1, SW2.1, U2.30 (PB6)
col3: S1.2
row0: D2.1 (K), D3.1 (K), D4.1 (K), D8.1 (K), U2.20 (PD2)
row1: D5.1 (K), D6.1 (K), D7.1 (K), U2.21 (PD3)

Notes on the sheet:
Switch matrix
555 timer

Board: 2 copper layers, 43 parts (0 on the bottom side), 42 nets, no tracks yet.
